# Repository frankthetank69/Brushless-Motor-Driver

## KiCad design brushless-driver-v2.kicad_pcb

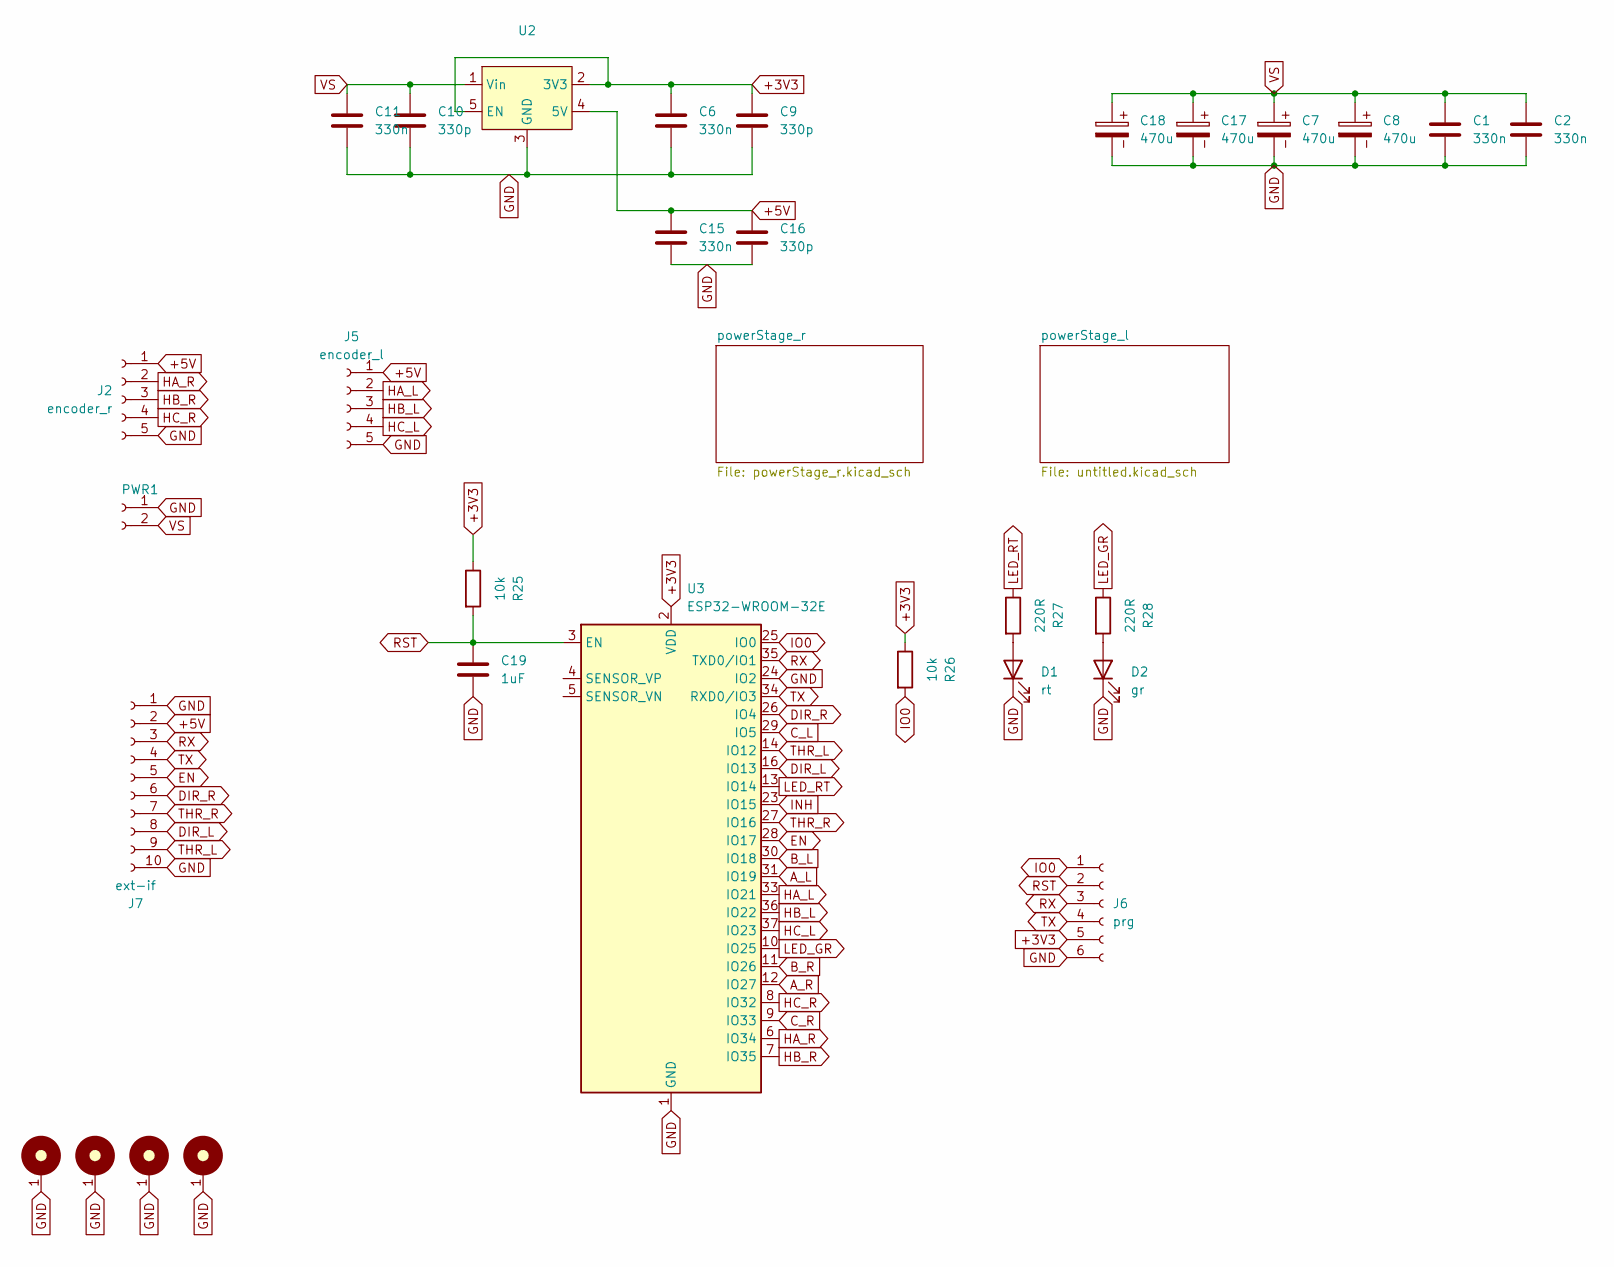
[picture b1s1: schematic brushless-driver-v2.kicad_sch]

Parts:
C1, C2, C6, C11, C15: 330n; C_0805_2012Metric_Pad1.18x1.45mm_HandSolder
C7, C8, C17, C18: 470u; CP_Radial_D10.0mm_P5.00mm
C9, C10, C16: 330p; C_0805_2012Metric_Pad1.18x1.45mm_HandSolder
C19: 1uF; C_0805_2012Metric_Pad1.18x1.45mm_HandSolder
D1: rt; LED_0805_2012Metric_Pad1.15x1.40mm_HandSolder
D2: gr; LED_0805_2012Metric_Pad1.15x1.40mm_HandSolder
H1, H2, H3, H4: MountingHole_M3_3.2mm_Pad; MountingHole_3.5mm_Pad_Via
J2: encoder_r; JST_PH_S5B-PH-K_1x05_P2.00mm_Horizontal
J5: encoder_l; JST_PH_S5B-PH-K_1x05_P2.00mm_Horizontal
J6: prg; Wannenstecker_6pin
J7: ext-if; Wannenstecker_10pin
PWR1: Conn_01x02_Socket; TerminalBlock_MaiXu_MX126-5.0-02P_1x02_P5.00mm
R25, R26: 10k; R_0805_2012Metric_Pad1.20x1.40mm_HandSolder
R27, R28: 220R; R_0805_2012Metric_Pad1.20x1.40mm_HandSolder
U2: TO-252-5-11
U3: ESP32-WROOM-32E; ESP32-WROOM-32D

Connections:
+3V3: C6.1, C9.1, J6.5, R25.1, R26.1, U2.2 (3V3), U2.5 (EN), U3.2 (VDD)
+5V: C15.1, C16.1, J2.1, J5.1, J7.2, U2.4 (5V)
A_L: U3.31 (IO19); also elsewhere on the board
A_R: U3.12 (IO27); also elsewhere on the board
B_L: U3.30 (IO18); also elsewhere on the board
B_R: U3.11 (IO26); also elsewhere on the board
C_L: U3.29 (IO5); also elsewhere on the board
C_R: U3.9 (IO33); also elsewhere on the board
DIR_L: J7.8, U3.16 (IO13)
DIR_R: J7.6, U3.26 (IO4)
EN: J7.5, U3.28 (IO17)
GND: C1.2, C2.2, C6.2, C7.2, C8.2, C9.2, C10.2, C11.2, C15.2, C16.2, C17.2, C18.2, C19.2, D1.1 (K), D2.1 (K), H1.1, H2.1, H3.1, H4.1, J2.5, J5.5, J6.6, J7.1, J7.10, PWR1.1, U2.3 (GND), U3.1 (GND), U3.15 (GND), U3.24 (IO2), U3.38 (GND), U3.39 (GND); also elsewhere on the board
HA_L: J5.2, U3.33 (IO21)
HA_R: J2.2, U3.6 (IO34)
HB_L: J5.3, U3.36 (IO22)
HB_R: J2.3, U3.7 (IO35)
HC_L: J5.4, U3.37 (IO23)
HC_R: J2.4, U3.8 (IO32)
INH: U3.23 (IO15); also elsewhere on the board
IO0: J6.1, R26.2, U3.25 (IO0)
LED_GR: R28.1, U3.10 (IO25)
LED_RT: R27.1, U3.13 (IO14)
unnamed: D1.2 (A), R27.2
unnamed: D2.2 (A), R28.2
RST: C19.1, J6.2, R25.2, U3.3 (EN)
RX: J6.3, J7.3, U3.35 (TXD0/IO1)
THR_L: J7.9, U3.14 (IO12)
THR_R: J7.7, U3.27 (IO16)
TX: J6.4, J7.4, U3.34 (RXD0/IO3)
VS: C1.1, C2.1, C7.1, C8.1, C10.1, C11.1, C17.1, C18.1, PWR1.2, U2.1 (Vin); also elsewhere on the board

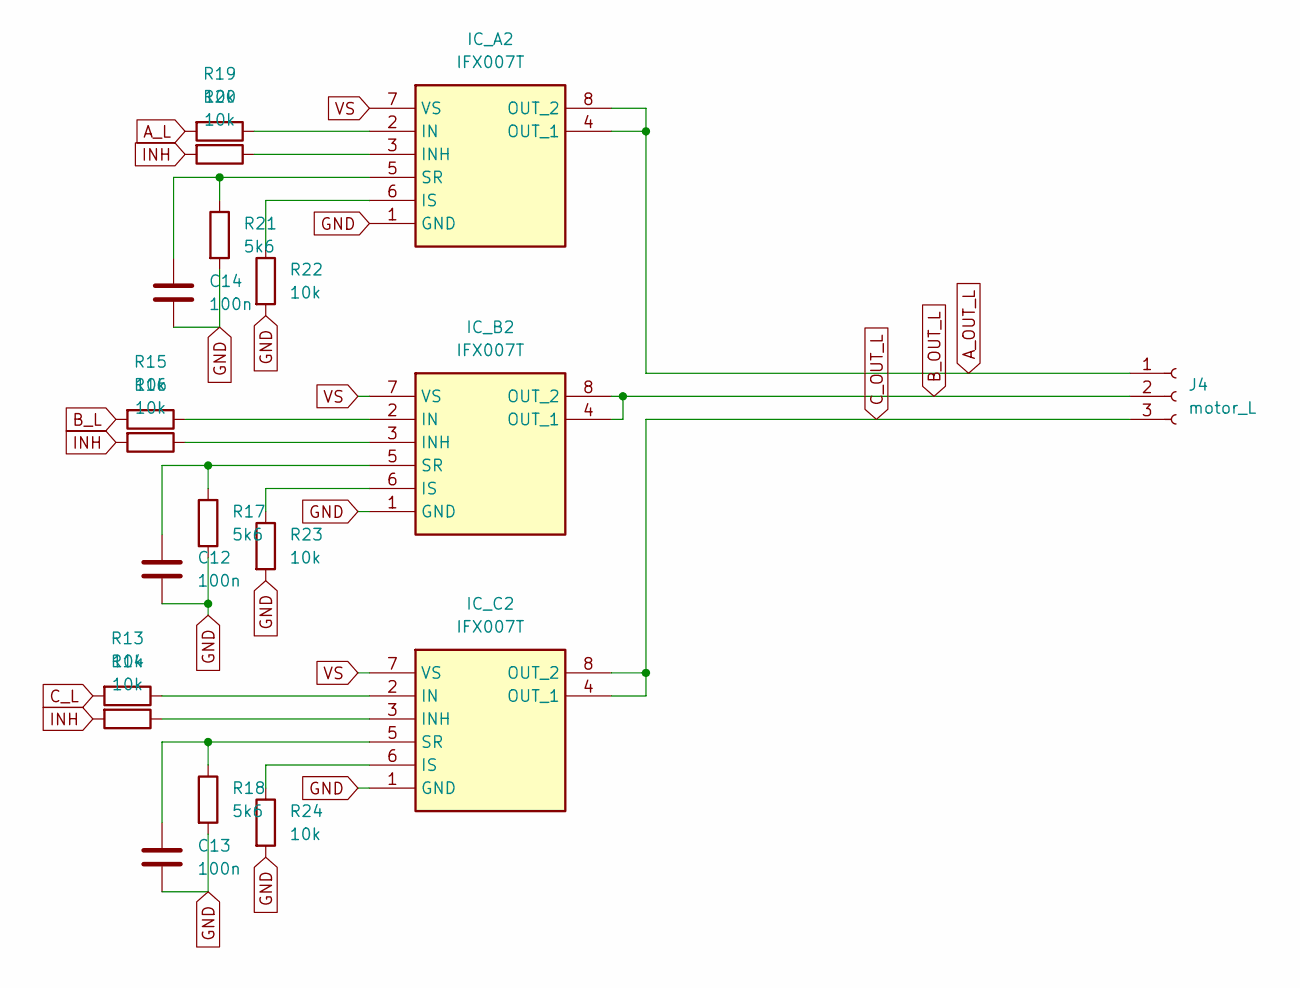
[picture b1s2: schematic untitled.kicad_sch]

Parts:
C12, C13, C14: 100n; C_0805_2012Metric_Pad1.18x1.45mm_HandSolder
IC_A2: IFX007T; TO-263-7_TabPin4; Manufacturer_Part_Number IFX007TAUMA1; Mouser Part Number 726-IFX007TAUMA1
IC_B2: IFX007T; TO-263-7_TabPin4; Manufacturer_Part_Number IFX007TAUMA1; Mouser Part Number 726-IFX007TAUMA1
IC_C2: IFX007T; TO-263-7_TabPin4; Manufacturer_Part_Number IFX007TAUMA1; Mouser Part Number 726-IFX007TAUMA1
J4: motor_L; TerminalBlock_MaiXu_MX126-5.0-03P_1x03_P5.00mm
R13, R14, R15, R16, R19, R20, R22, R23, R24: 10k; R_0805_2012Metric_Pad1.20x1.40mm_HandSolder
R17, R18, R21: 5k6; R_0805_2012Metric_Pad1.20x1.40mm_HandSolder

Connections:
A_L: R19.2; also elsewhere on the board
A_OUT_L: IC_A2.4 (OUT_1), IC_A2.8 (OUT_2), J4.1
B_L: R15.2; also elsewhere on the board
B_OUT_L: IC_B2.4 (OUT_1), IC_B2.8 (OUT_2), J4.2
C_L: R13.2; also elsewhere on the board
C_OUT_L: IC_C2.4 (OUT_1), IC_C2.8 (OUT_2), J4.3
GND: C12.2, C13.2, C14.2, IC_A2.1 (GND), IC_B2.1 (GND), IC_C2.1 (GND), R17.2, R18.2, R21.2, R22.2, R23.2, R24.2; also elsewhere on the board
INH: R14.2, R16.2, R20.2; also elsewhere on the board
unnamed: IC_A2.2 (IN), R19.1
unnamed: IC_A2.3 (INH), R20.1
unnamed: IC_A2.6 (IS), R22.1
unnamed: C14.1, IC_A2.5 (SR), R21.1
unnamed: IC_B2.2 (IN), R15.1
unnamed: IC_B2.3 (INH), R16.1
unnamed: IC_B2.6 (IS), R23.1
unnamed: C12.1, IC_B2.5 (SR), R17.1
unnamed: IC_C2.2 (IN), R13.1
unnamed: IC_C2.3 (INH), R14.1
unnamed: IC_C2.6 (IS), R24.1
unnamed: C13.1, IC_C2.5 (SR), R18.1
VS: IC_A2.7 (VS), IC_B2.7 (VS), IC_C2.7 (VS); also elsewhere on the board

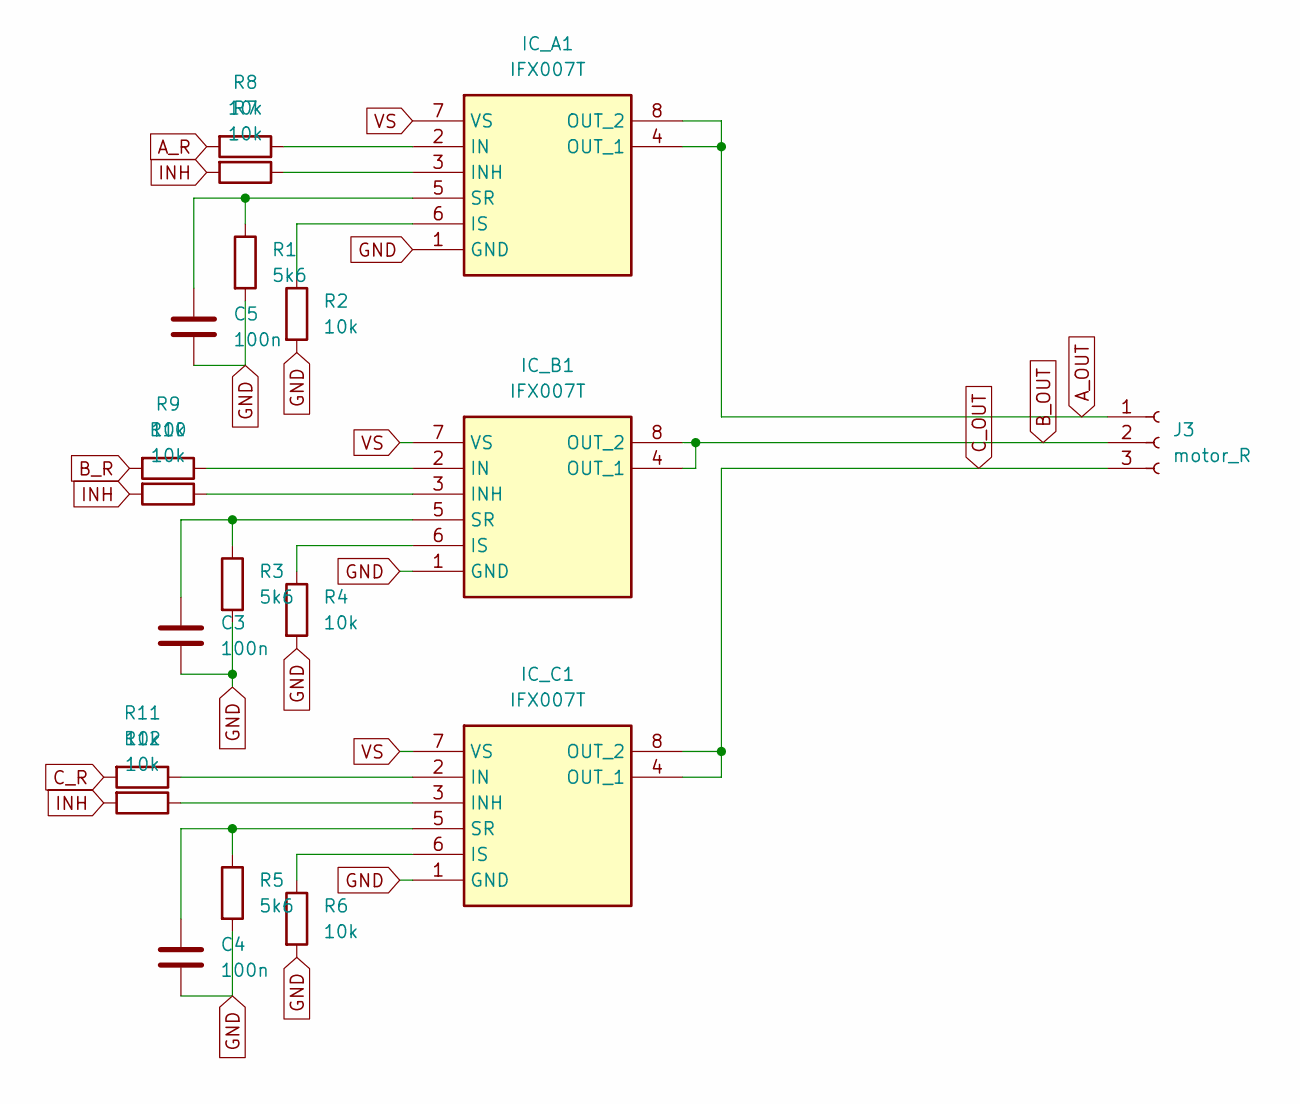
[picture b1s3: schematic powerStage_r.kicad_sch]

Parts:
C3, C4, C5: 100n; C_0805_2012Metric_Pad1.18x1.45mm_HandSolder
IC_A1: IFX007T; TO-263-7_TabPin4; Manufacturer_Part_Number IFX007TAUMA1; Mouser Part Number 726-IFX007TAUMA1
IC_B1: IFX007T; TO-263-7_TabPin4; Manufacturer_Part_Number IFX007TAUMA1; Mouser Part Number 726-IFX007TAUMA1
IC_C1: IFX007T; TO-263-7_TabPin4; Manufacturer_Part_Number IFX007TAUMA1; Mouser Part Number 726-IFX007TAUMA1
J3: motor_R; TerminalBlock_MaiXu_MX126-5.0-03P_1x03_P5.00mm
R1, R3, R5: 5k6; R_0805_2012Metric_Pad1.20x1.40mm_HandSolder
R2, R4, R6, R7, R8, R9, R10, R11, R12: 10k; R_0805_2012Metric_Pad1.20x1.40mm_HandSolder

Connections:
A_OUT: IC_A1.4 (OUT_1), IC_A1.8 (OUT_2), J3.1
A_R: R8.2; also elsewhere on the board
B_OUT: IC_B1.4 (OUT_1), IC_B1.8 (OUT_2), J3.2
B_R: R9.2; also elsewhere on the board
C_OUT: IC_C1.4 (OUT_1), IC_C1.8 (OUT_2), J3.3
C_R: R11.2; also elsewhere on the board
GND: C3.2, C4.2, C5.2, IC_A1.1 (GND), IC_B1.1 (GND), IC_C1.1 (GND), R1.2, R2.2, R3.2, R4.2, R5.2, R6.2; also elsewhere on the board
INH: R7.2, R10.2, R12.2; also elsewhere on the board
unnamed: IC_A1.2 (IN), R8.1
unnamed: IC_A1.3 (INH), R7.1
unnamed: IC_A1.6 (IS), R2.1
unnamed: C5.1, IC_A1.5 (SR), R1.1
unnamed: IC_B1.2 (IN), R9.1
unnamed: IC_B1.3 (INH), R10.1
unnamed: IC_B1.6 (IS), R4.1
unnamed: C3.1, IC_B1.5 (SR), R3.1
unnamed: IC_C1.2 (IN), R11.1
unnamed: IC_C1.3 (INH), R12.1
unnamed: IC_C1.6 (IS), R6.1
unnamed: C4.1, IC_C1.5 (SR), R5.1
VS: IC_A1.7 (VS), IC_B1.7 (VS), IC_C1.7 (VS); also elsewhere on the board

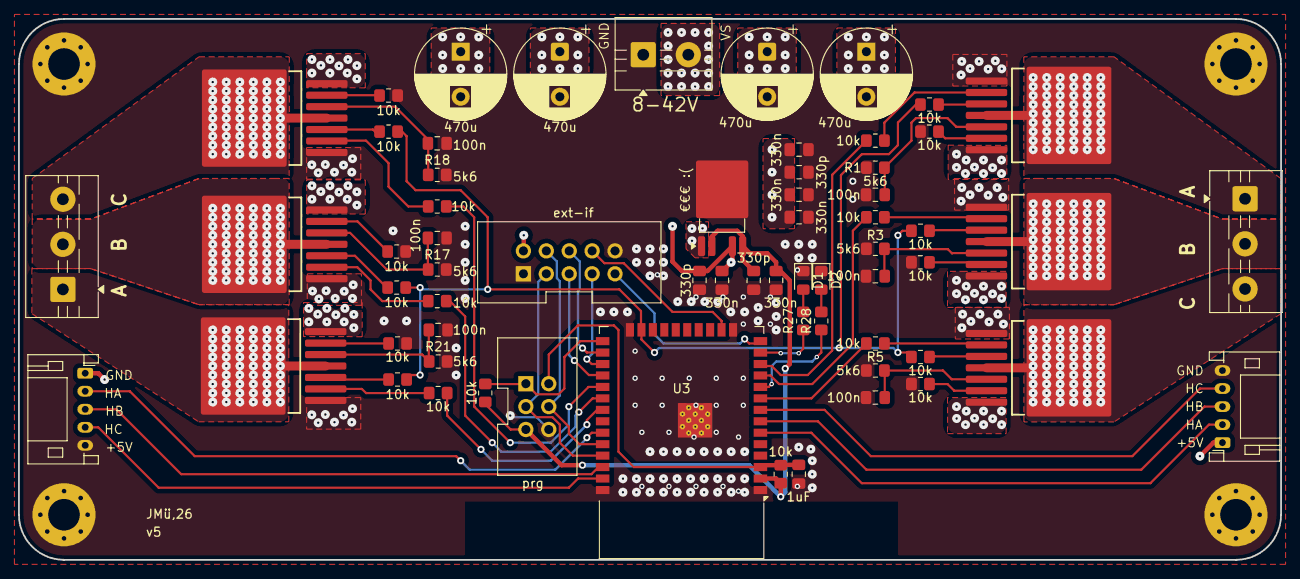
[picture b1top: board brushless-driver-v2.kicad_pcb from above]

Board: 4 copper layers, 140.0 x 60.0 mm, 68 parts (0 on the bottom side), 60 nets.
